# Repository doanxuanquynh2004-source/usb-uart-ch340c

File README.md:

# USB Type-C to UART TTL — CH340C

Đồ án thiết kế mạch chuyển đổi USB sang UART TTL sử dụng **CH340C**, thực hiện trên **KiCad 10**. Mạch kết nối với máy tính qua cổng USB Type-C và đưa tín hiệu UART ra header 4 chân.

**Trạng thái:** đã hoàn thành sơ đồ nguyên lý và bố trí PCB; đang chuẩn bị chế tạo. Chưa có kết quả kiểm thử trên phần cứng đã lắp ráp.

## Sơ đồ nguyên lý

## Hình ảnh PCB

### Lớp đồng trên — F.Cu

### Lớp đồng dưới — B.Cu

Ảnh được dựng từ dữ liệu Gerber, có tô màu để phân biệt các net; đây là ảnh minh họa thiết kế. Cả hai ảnh dùng góc nhìn từ mặt trên, ảnh B.Cu là nhìn xuyên xuống lớp dưới.

## Chức năng thiết kế

- Chuyển đổi USB sang UART TTL bằng CH340C.
- Cấp nguồn 5 V từ USB.
- Đầu nối USB Type-C, dùng các đường dữ liệu USB 2.0 D+ và D−.
- Header UART gồm +5V, TX, RX và GND.
- LED nguồn và LED chỉ thị TX/RX.
- Hai điện trở 5,1 kΩ nối riêng CC1 và CC2 xuống GND.

Mạch được thiết kế cho UART TTL 5 V. Cần kiểm tra khả năng chịu điện áp của thiết bị đích trước khi nối tín hiệu UART.

## Thông số PCB

| Hạng mục | Giá trị trong thiết kế |
|---|---|
| Kích thước theo đường biên Edge.Cuts | 40,5 × 19 mm |
| Số lớp đồng | 2 |
| Độ dày khai báo | 1,6 mm |
| Độ dày đồng khai báo | 35 µm |
| Độ rộng đường mạch | 0,20 mm |
| Via: đường kính ngoài / lỗ khoan | 0,70 / 0,30 mm |
| Số linh kiện | 14 |

## Đầu nối UART — J2

| Chân | Tín hiệu | Chức năng |
|---|---|---|
| 1 | +5V | Đường nguồn 5 V từ USB |
| 2 | TX | Tín hiệu phát từ CH340C |
| 3 | RX | Tín hiệu nhận vào CH340C |
| 4 | GND | Mass chung |

Khi nối với thiết bị khác: TX của mạch nối RX của thiết bị, RX của mạch nối TX của thiết bị và nối chung GND. Việc sử dụng chân +5V phụ thuộc cách cấp nguồn của thiết bị đích.

## Danh sách linh kiện

| Ký hiệu | Linh kiện / giá trị | Kiểu vỏ hoặc đầu nối | Số lượng |
|---|---|---|---:|
| U1 | CH340C | SOIC-16, thân rộng 3,9 mm, bước chân 1,27 mm | 1 |
| J1 | USB Type-C USB 2.0 | HRO TYPE-C-31-M-12 | 1 |
| J2 | Header đực 1×4 | Thẳng, bước chân 2,54 mm, xuyên lỗ | 1 |
| R1, R2 | 5,1 kΩ | 0805 | 2 |
| R3, R6, R7 | 1 kΩ | 0805 | 3 |
| C1 | 10 µF | 0805 | 1 |
| C2, C3 | 100 nF | 0805 | 2 |
| D1 | LED nguồn | 0805 | 1 |
| D2 | LED TX | 0805 | 1 |
| D3 | LED RX | 0805 | 1 |

Danh sách trên lấy từ thiết kế KiCad. Mã đặt hàng cụ thể, điện áp định mức của tụ và màu LED cần được chốt khi mua linh kiện. Đầu nối USB phải khớp footprint đã chọn.

## Tệp dự án

| Tệp / thư mục | Nội dung |
|---|---|
| [hardware/USB_UART_CH340C.kicad_pro](hardware/USB_UART_CH340C.kicad_pro) | Tệp dự án KiCad |
| [hardware/USB_UART_CH340C.kicad_sch](hardware/USB_UART_CH340C.kicad_sch) | Sơ đồ nguyên lý |
| [hardware/USB_UART_CH340C.kicad_pcb](hardware/USB_UART_CH340C.kicad_pcb) | PCB đã bố trí và đi dây |
| [fabrication/Gerber_VN_2026-10-19.zip](fabrication/Gerber_VN_2026-10-19.zip) | Gerber và dữ liệu khoan của bản PCB này |
| [docs/images](docs/images) | Ảnh minh họa lớp đồng |
| [.gitignore](.gitignore) | Danh sách bỏ qua tệp tạm và bản sao lưu khi dùng Git |

Để mở và chỉnh sửa, tải toàn bộ repository, giải nén rồi mở `hardware/USB_UART_CH340C.kicad_pro` bằng KiCad 10 với bộ thư viện tiêu chuẩn.

## Quá trình thiết kế và kiểm tra

Tôi thực hiện dự án USB Type-C sang UART TTL sử dụng CH340C trên KiCad, từ xây dựng sơ đồ nguyên lý, lựa chọn footprint, bố trí linh kiện đến đi dây và đổ đồng PCB.

Trong quá trình hoàn thiện, tôi điều chỉnh thiết kế theo yêu cầu gia công của xưởng, với độ rộng đường mạch 0,20 mm và kích thước via 0,70 mm / lỗ khoan 0,30 mm. Tôi chủ động bố trí phần thân đầu nối USB Type-C nhô ra khỏi mép bo để thuận tiện cắm cáp.

### Kết quả kiểm tra trên KiCad

Tôi đã trực tiếp chạy **Design Rules Checker (DRC)** trên bản PCB cập nhật ngày **19/10/2026**.

**Kết quả: 0 Errors — không phát hiện lỗi theo bộ quy tắc thiết kế được cấu hình tại thời điểm kiểm tra.**

Sau khi hoàn tất kiểm tra, tôi xuất các lớp Gerber và dữ liệu khoan để chuẩn bị gia công PCB.

### Trạng thái dự án

Dự án đã hoàn thành giai đoạn thiết kế PCB và kiểm tra DRC trên KiCad. Tôi sẽ cập nhật ảnh bo mạch thực tế, kết quả nhận cổng COM và kiểm thử giao tiếp UART sau khi chế tạo và lắp ráp.

## Kế hoạch kiểm thử sau lắp ráp

- [ ] Kiểm tra chất lượng mối hàn, chiều IC và LED.
- [ ] Kiểm tra chạm chập nguồn trước khi cấp điện.
- [ ] Xác nhận máy tính nhận cổng COM của CH340C.
- [ ] Kiểm tra UART loopback bằng cách nối TX với RX.
- [ ] Kiểm tra giao tiếp với thiết bị đích và ghi lại baud rate, kết quả đo, ảnh thực tế.

Các mục trên là kế hoạch; kết quả sẽ được cập nhật sau khi có bo mạch thực tế.

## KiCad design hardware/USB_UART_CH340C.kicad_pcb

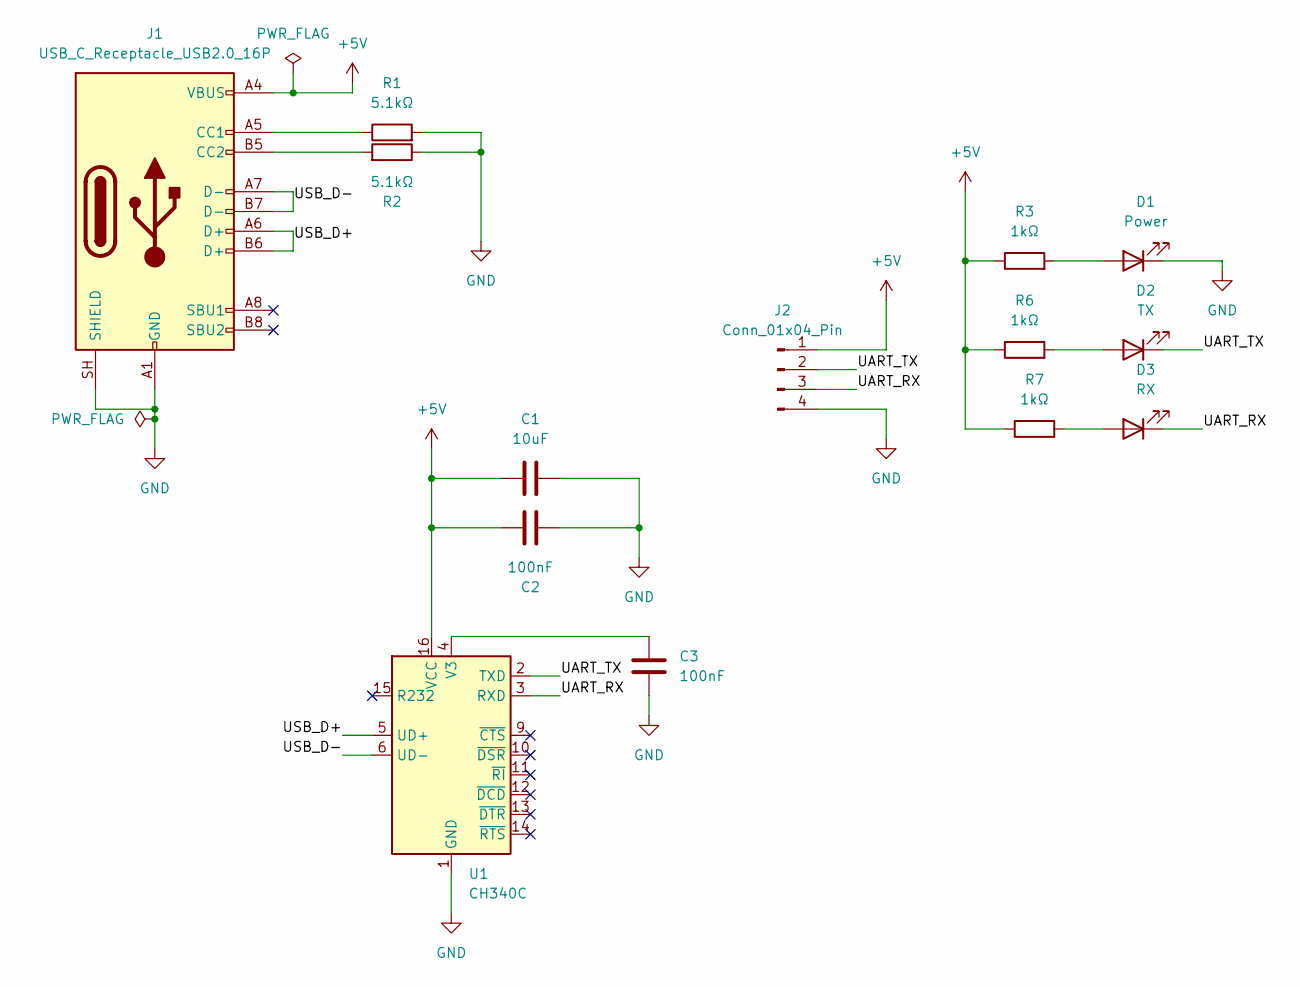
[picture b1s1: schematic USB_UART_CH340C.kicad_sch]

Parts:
C1: 10uF; C_0805_2012Metric
C2, C3: 100nF; C_0805_2012Metric
D1: Power; LED_0805_2012Metric
D2: TX; LED_0805_2012Metric
D3: RX; LED_0805_2012Metric
J1: USB_C_Receptacle_USB2.0_16P; USB_C_Receptacle_HRO_TYPE-C-31-M-12
J2: Conn_01x04_Pin; PinHeader_1x04_P2.54mm_Vertical
R1, R2: 5.1kΩ; R_0805_2012Metric
R3, R6, R7: 1kΩ; R_0805_2012Metric
U1: CH340C; SOIC-16_3.9x9.9mm_P1.27mm

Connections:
+5V: C1.2, C2.1, J1.A4 (VBUS), J1.A9 (VBUS), J1.B4 (VBUS), J1.B9 (VBUS), J2.1, R3.1, R6.1, R7.1, U1.16 (VCC)
/UART_RX: D3.1 (K), J2.3, U1.3 (RXD)
/UART_TX: D2.1 (K), J2.2, U1.2 (TXD)
/USB_D+: J1.A6 (D+), J1.B6 (D+), U1.5 (UD+)
/USB_D-: J1.A7 (D-), J1.B7 (D-), U1.6 (UD-)
GND: C1.1, C2.2, C3.2, D1.1 (K), J1.A1 (GND), J1.A12 (GND), J1.B1 (GND), J1.B12 (GND), J1.SH (SHIELD), J2.4, R1.2, R2.1, U1.1 (GND)
unnamed: D1.2 (A), R3.2
unnamed: D2.2 (A), R6.2
unnamed: D3.2 (A), R7.2
unnamed: J1.A5 (CC1), R1.1
unnamed: J1.B5 (CC2), R2.2
unnamed: C3.1, U1.4 (V3)

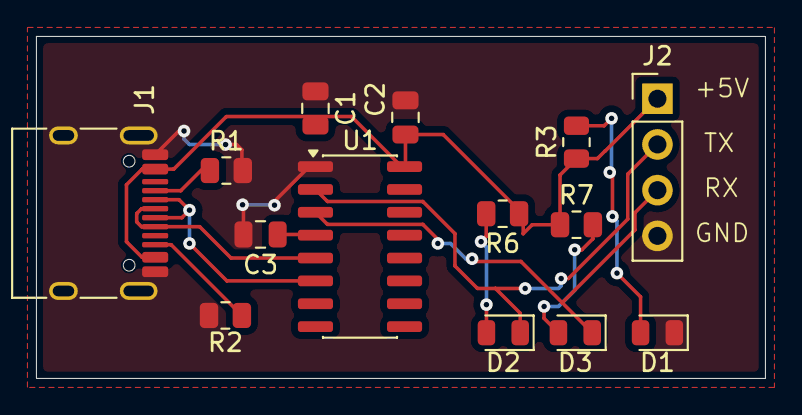
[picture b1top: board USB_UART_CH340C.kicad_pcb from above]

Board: 2 copper layers, 40.5 x 19.0 mm, 14 parts (0 on the bottom side), 12 nets.
